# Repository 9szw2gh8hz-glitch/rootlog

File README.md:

# rootlog
## The Privacy-First, Local Data Logging Solution

RootLog is a dedicated environmental monitoring system designed to put data ownership back into the hands of the user. Unlike cloud-based smart home sensors, RootLog operates 100% locally. It monitors ambient conditions and air quality, storing every data point on a MicroSD card for private analysis.
Project Description

    Privacy-Focused: No Wi-Fi required; no data ever leaves the device.

    Robust Logging: Saves data to a MicroSD card every 60 seconds.

    Data Integrity: Features a "Flush" strategy that physically saves data to the card every 5 minutes to prevent loss during power failure.

    Power Management: Supports a Deep Sleep mode (activated by a 2-second button hold) to conserve battery during portable use.

    Multi-View Display: A 0.91" OLED screen cycles through 4 distinct data pages with a single tap.

## BOM

    Microcontroller: ESP32-C3 SuperMini

    Environmental Sensor: BME280 (Temp, Hum, Pres)

    Air Quality Sensor: SGP30 (eCO2, TVOC)

    Real-Time Clock: DS3231 RTC

    Display: 0.91" I2C OLED (128x32)

    Storage: MicroSD Card Module

## Wiring Map

Component	Pin Function	ESP32-C3 Pin
I2C Bus	SDA	GPIO 8
I2C Bus	SCL	GPIO 9
MicroSD	CS (Chip Select)	GPIO 7
MicroSD	MOSI	GPIO 6
MicroSD	MISO	GPIO 5
MicroSD	SCK (Clock)	GPIO 4
Control	Push Button	GPIO 2
Software & Setup
Required Libraries

## Usage Instructions

    Boot: Upon power-up, the OLED will display "ROOTLOG BOOTING..." while initializing sensors.

    Cycle Pages: Short-press the button to cycle between:

        Temperature (°C)

        Humidity (%) and Pressure (hPa)

        Air Quality (eCO2 ppm and TVOC ppb)

        Current System Time

    Power Off: Hold the button for 2 seconds. The screen will show "BYE BYE" and enter deep sleep.

    Wake Up: Press the button again to resume logging.

    Note on Calibration: The SGP30 air quality sensor requires approximately 15 seconds of operation to stabilize its internal baseline before reporting accurate eCO2 and TVOC values.

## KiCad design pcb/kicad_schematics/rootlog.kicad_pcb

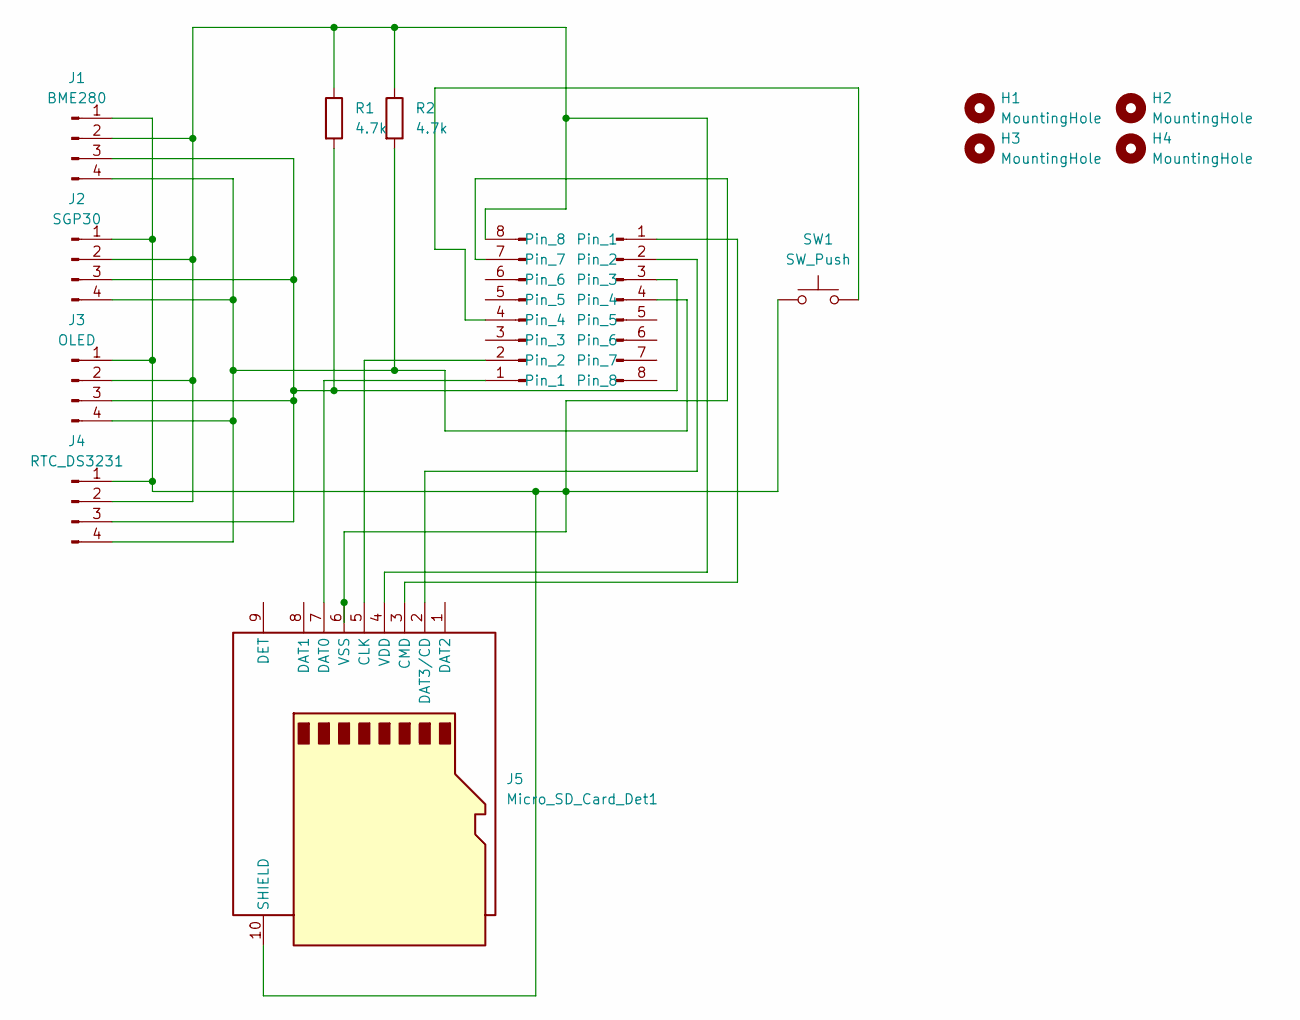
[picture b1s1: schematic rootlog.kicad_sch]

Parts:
H1, H2, H3, H4: MountingHole; MountingHole_3.2mm_M3
J1: BME280; FanPinHeader_1x04_P2.54mm_Vertical
J2: SGP30; FanPinHeader_1x04_P2.54mm_Vertical
J3: OLED; FanPinHeader_1x04_P2.54mm_Vertical
J4: RTC_DS3231; FanPinHeader_1x04_P2.54mm_Vertical
J5: Micro_SD_Card_Det1; microSD_HC_Hirose_DM3D-SF
J6, J7: Conn_01x08_Pin; PinHeader_1x08_P2.54mm_Vertical
R1, R2: 4.7k; R_Axial_DIN0207_L6.3mm_D2.5mm_P2.54mm_Vertical
SW1: SW_Push; SW_PUSH_6mm_H4.3mm

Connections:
unnamed: J1.1, J2.1, J3.1, J4.1, J5.6 (VSS), J5.10 (SHIELD), J6.7, SW1.1
unnamed: J1.2, J2.2, J3.2, J4.2, J5.4 (VDD), J6.8, R1.1, R2.1
unnamed: J1.3, J2.3, J3.3, J4.3, J7.3, R1.2
unnamed: J1.4, J2.4, J3.4, J4.4, J7.4, R2.2
unnamed: J5.5 (CLK), J6.2
unnamed: J5.3 (CMD), J7.1
unnamed: J5.7 (DAT0), J6.1
unnamed: J5.2 (DAT3/CD), J7.2
unnamed: J6.4, SW1.2

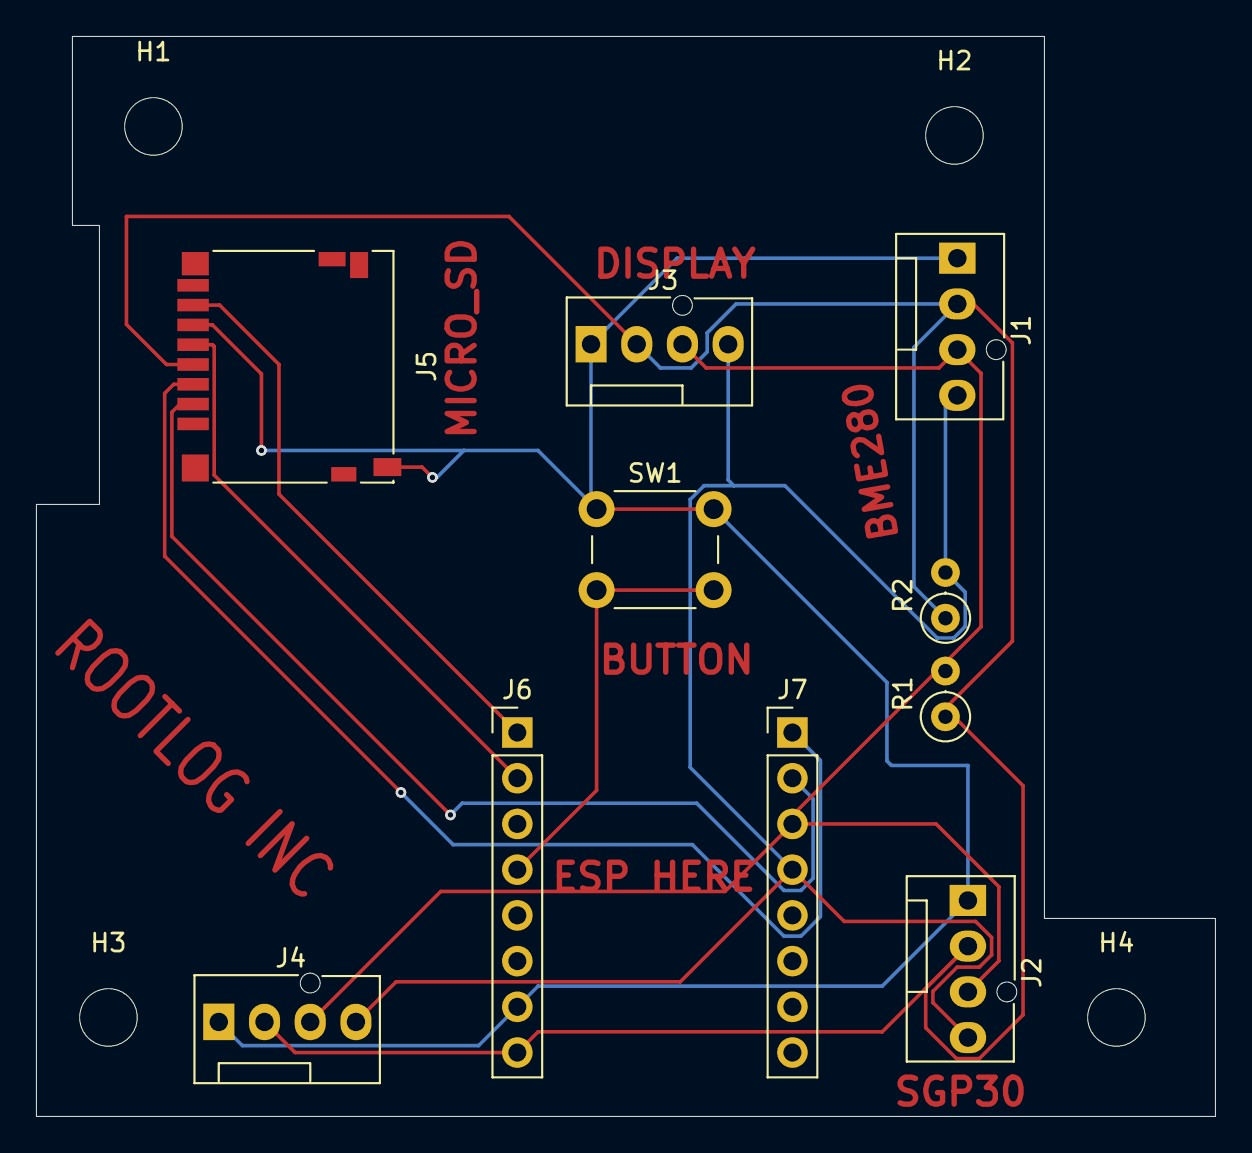
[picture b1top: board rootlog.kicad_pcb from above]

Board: 2 copper layers, 65.5 x 60.0 mm, 14 parts (0 on the bottom side), 9 nets.

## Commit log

2026-01-16 Create temp
